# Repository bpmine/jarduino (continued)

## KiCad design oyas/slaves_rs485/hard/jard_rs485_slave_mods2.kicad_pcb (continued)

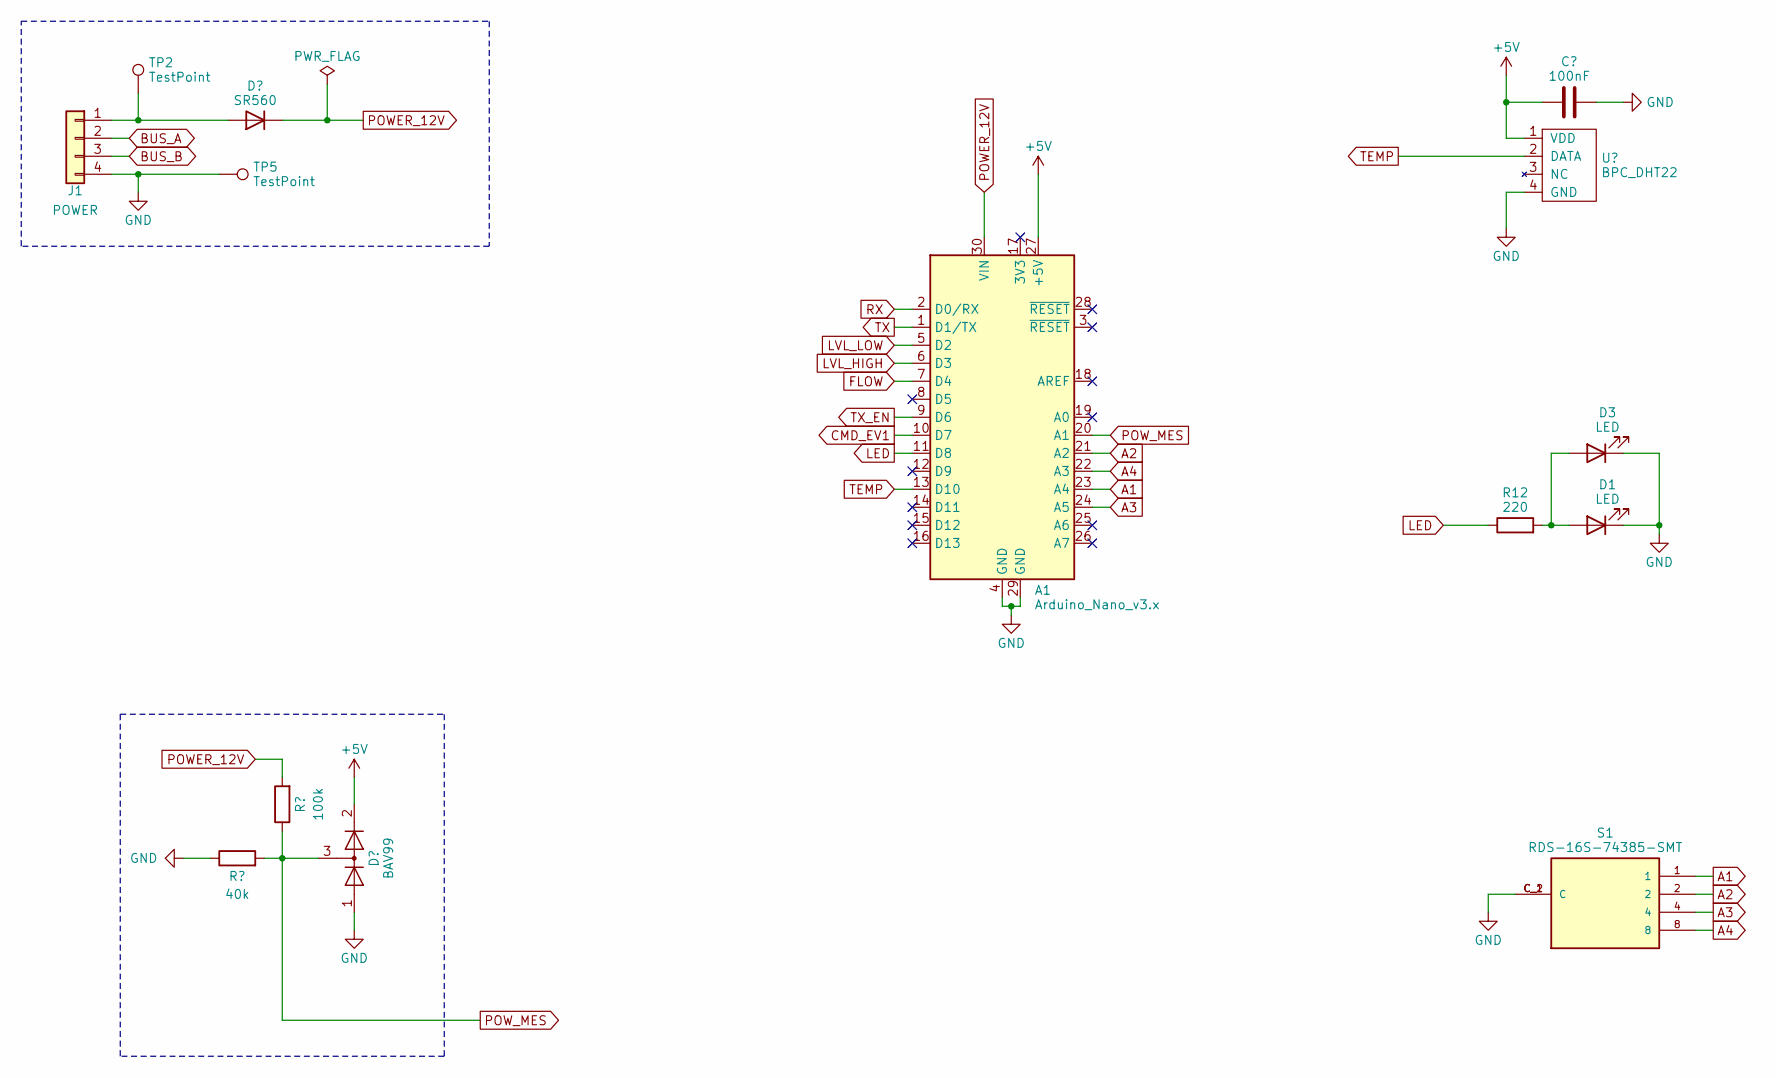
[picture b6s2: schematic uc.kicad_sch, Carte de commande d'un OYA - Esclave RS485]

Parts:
A1: Arduino_Nano_v3.x; BPC_Arduino_Nano
C7: 100nF; C_0603_1608Metric
D1: LED; LED_0805_2012Metric_Pad1.15x1.40mm_HandSolder
D2: SR560; D_DO-15_P12.70mm_Horizontal
D3: LED; LED_D3.0mm_FlatTop
D5: BAV99; SOT-23
J1: POWER; TerminalBlock_Phoenix_MKDS-1,5-4-5.08_1x04_P5.08mm_Horizont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
R1: 40k; R_0805_2012Metric_Pad1.20x1.40mm_HandSolder
R2: 100k; R_0805_2012Metric_Pad1.20x1.40mm_HandSolder
R12: 220; R_0805_2012Metric_Pad1.20x1.40mm_HandSolder
S1: RDS-16S-74385-SMT; BPC_RDS-16S-74385-SMT; PARTREV 1.0
TP2, TP5: TestPoint; TestPoint_Pad_D1.5mm
U6: BPC_DHT22

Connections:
+5V: A1.27 (+5V), C7.1, D5.2 (A), U6.1 (VDD); also elsewhere on the board
A1: A1.23 (A4), S1.1
A2: A1.21 (A2), S1.2
A3: A1.24 (A5), S1.4
A4: A1.22 (A3), S1.8
CMD_EV1: A1.10 (D7); also elsewhere on the board
FLOW: A1.7 (D4); also elsewhere on the board
GND: A1.4 (GND), A1.29 (GND), C7.2, D1.1 (K), D3.1 (K), D5.1 (K), J1.4, R1.1, S1.C_1 (C), S1.C_2 (C), TP5.1, U6.4 (GND); also elsewhere on the board
LED: A1.11 (D8), R12.1
LVL_HIGH: A1.6 (D3); also elsewhere on the board
LVL_LOW: A1.5 (D2); also elsewhere on the board
unnamed: D1.2 (A), D3.2 (A), R12.2
unnamed: D2.2 (A), J1.1, TP2.1
POWER_12V: A1.30 (VIN), D2.1 (K), R2.2; also elsewhere on the board
POW_MES: A1.20 (A1), D5.3 (K), R1.2, R2.1
TEMP: A1.13 (D10), U6.2 (DATA)
TX: A1.1 (D1/TX); also elsewhere on the board
TX_EN: A1.9 (D6); also elsewhere on the board

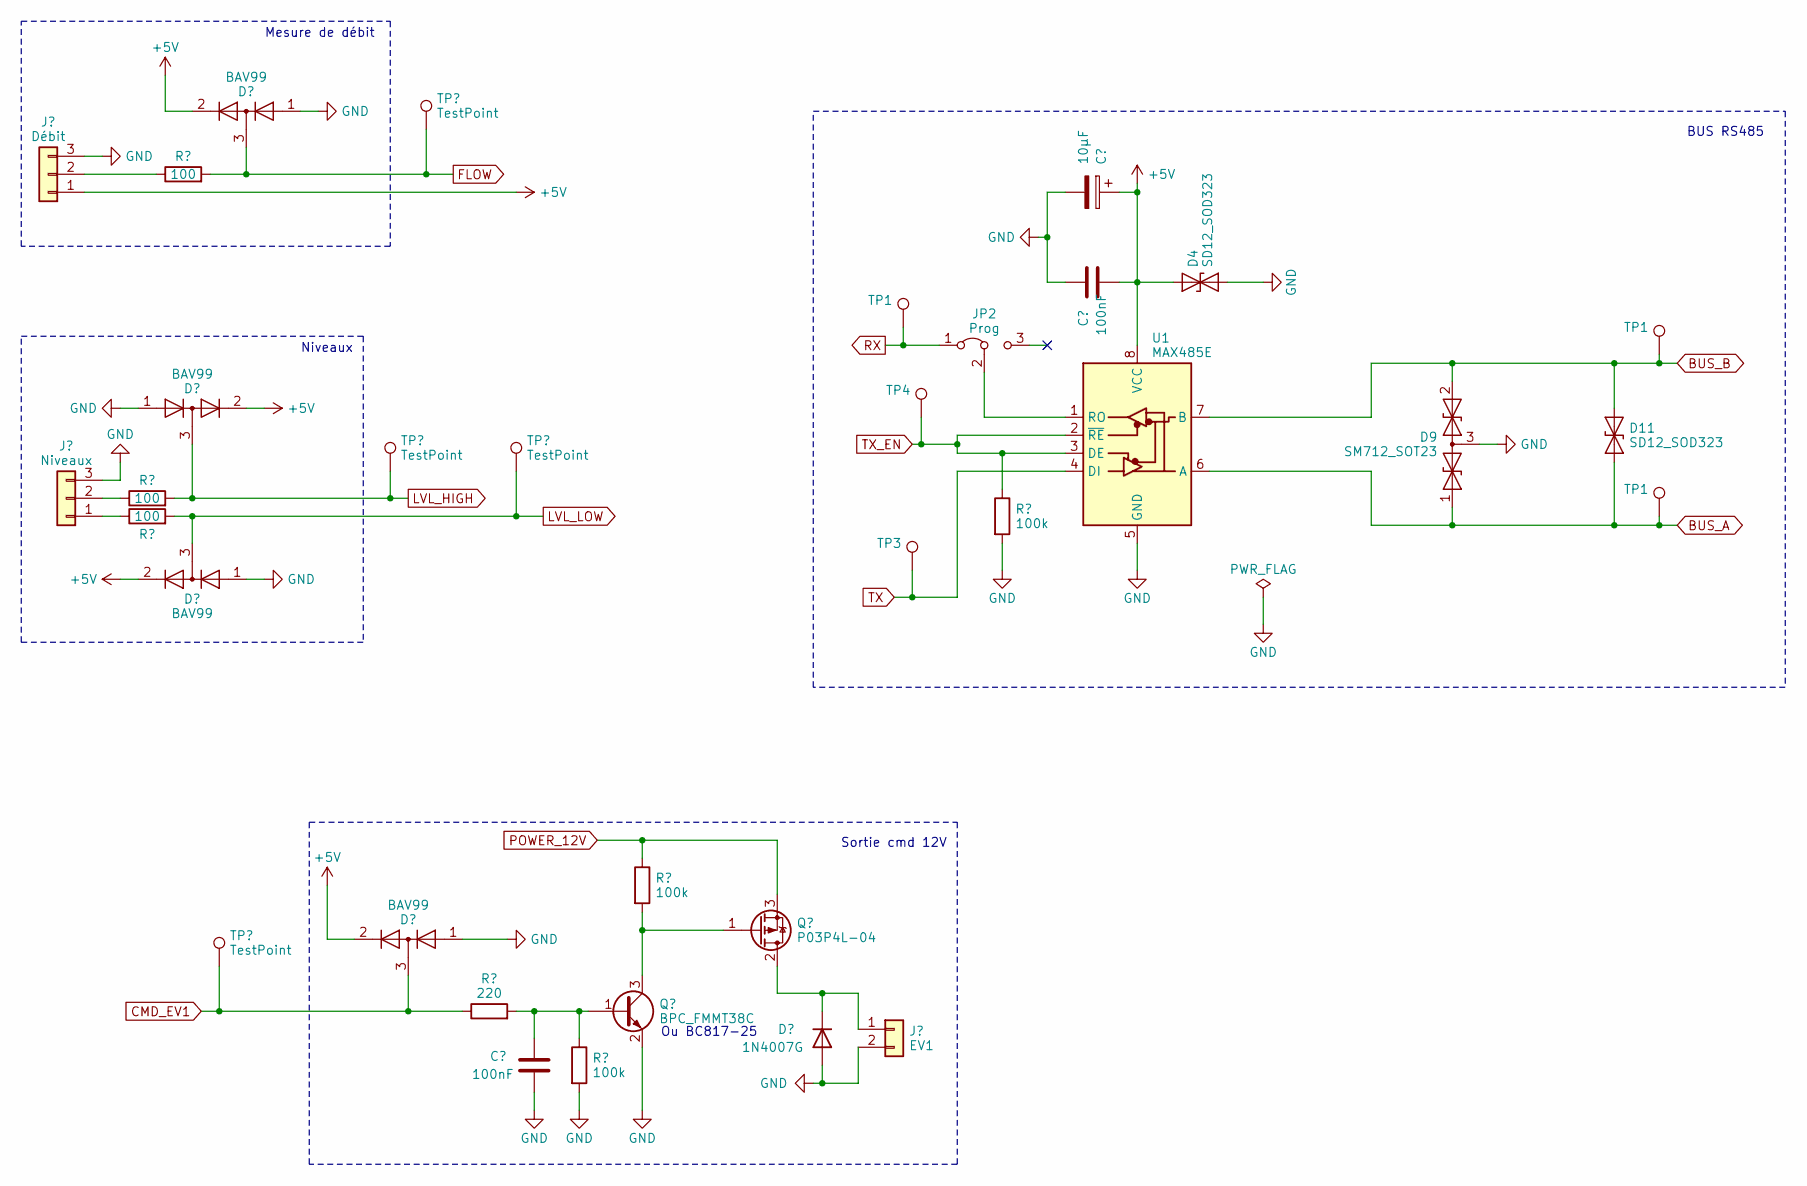
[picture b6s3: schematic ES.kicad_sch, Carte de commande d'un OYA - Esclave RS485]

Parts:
C1: 10µF; C_0805_2012Metric
C2, C6: 100nF; C_0603_1608Metric
D4, D11: SD12_SOD323; D_SOD-323
D6, D7, D8, D10: BAV99; SOT-23
D9: SM712_SOT23; SOT-23
D13: 1N4007G; D_A-405_P5.08mm_Vertical_KathodeUp
J3: Débit; TerminalBlock_Phoenix_MPT-0,5-3-2.54_1x03_P2.54mm_Horizontal
J4: Niveaux; TerminalBlock_Phoenix_MPT-0,5-3-2.54_1x03_P2.54mm_Horizontal
J6: EV1; TerminalBlock_Phoenix_MPT-0,5-2-2.54_1x02_P2.54mm_Horizontal
JP2: Prog; PinHeader_1x03_P2.54mm_Vertical
Q4: BPC_FMMT38C; BPC_SOT-23-3
Q6: P03P4L-04; TO-220-3_Vertical
R3, R15, R17: 100k; R_0805_2012Metric_Pad1.20x1.40mm_HandSolder
R7, R8, R9: 100; R_0805_2012Metric_Pad1.20x1.40mm_HandSolder
R13: 220; R_0805_2012Metric_Pad1.20x1.40mm_HandSolder
TP1, TP3, TP4, TP11, TP12, TP13, TP15: TestPoint; TestPoint_Pad_D1.5mm
U1: MAX485E; BPC_MAX485E_SOIC127P600X175-8N

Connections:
+5V: C1.1, C2.2, D4.1 (A1), D6.2 (A), D7.2 (A), D8.2 (A), D10.2 (A), J3.1, U1.8 (VCC); also elsewhere on the board
CMD_EV1: D10.3 (K), R13.1, TP15.1; also elsewhere on the board
FLOW: D8.3 (K), R7.2, TP11.1; also elsewhere on the board
GND: C1.2, C2.1, C6.2, D4.2 (A2), D6.1 (K), D7.1 (K), D8.1 (K), D9.3 (common), D10.1 (K), D13.2 (A), J3.3, J4.3, J6.2, Q4.2 (E), R3.2, R15.2, U1.5 (GND); also elsewhere on the board
LVL_HIGH: D6.3 (K), R8.2, TP12.1; also elsewhere on the board
LVL_LOW: D7.3 (K), R9.2, TP13.1; also elsewhere on the board
unnamed: D13.1 (K), J6.1, Q6.2 (D)
unnamed: J3.2, R7.1
unnamed: J4.1, R9.1
unnamed: J4.2, R8.1
unnamed: JP2.2 (C), U1.1 (RO)
unnamed: C6.1, Q4.1 (B), R13.2, R15.1
unnamed: Q4.3 (C), Q6.1 (G), R17.2
POWER_12V: Q6.3 (S), R17.1; also elsewhere on the board
TX: TP3.1, U1.4 (DI); also elsewhere on the board
TX_EN: R3.1, TP4.1, U1.2 (~RE), U1.3 (DE); also elsewhere on the board

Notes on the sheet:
Mesure de débit
Ou BC817-25
BUS RS485
Sortie cmd 12V
Niveaux

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
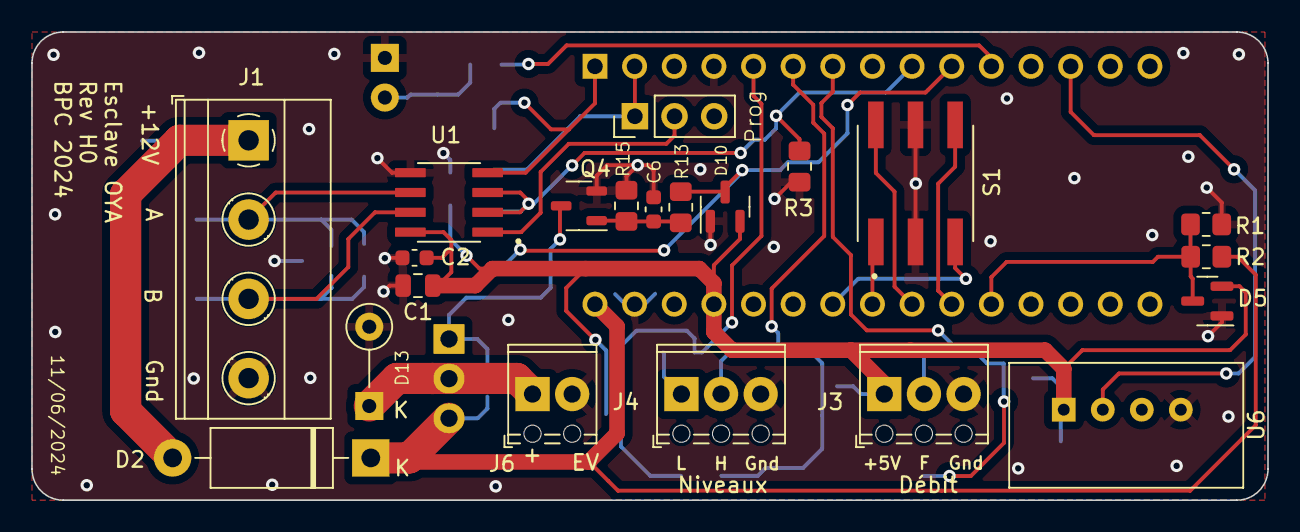
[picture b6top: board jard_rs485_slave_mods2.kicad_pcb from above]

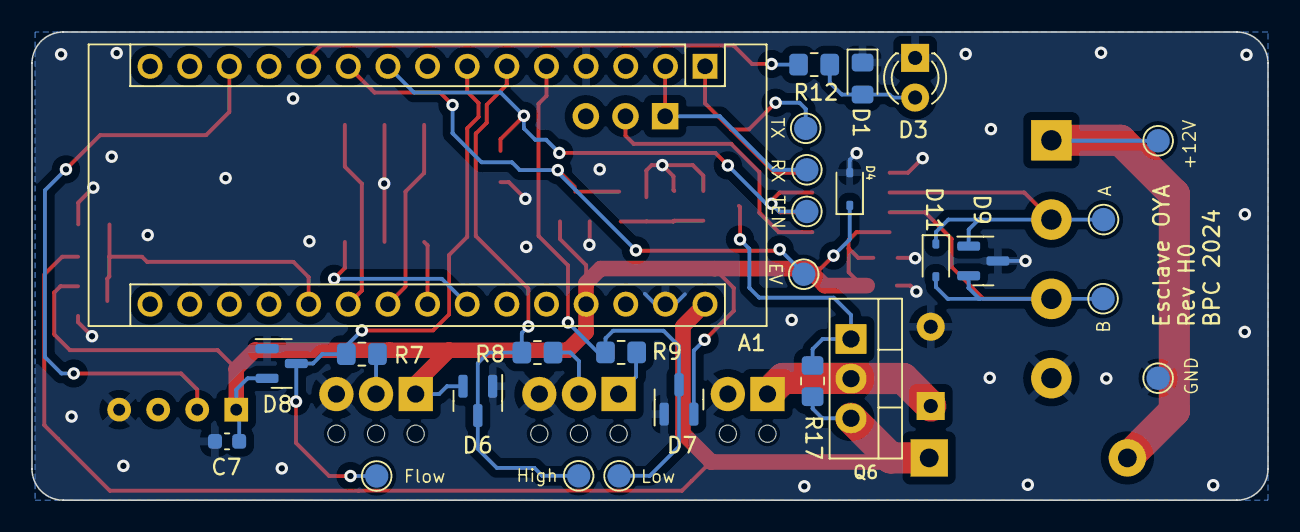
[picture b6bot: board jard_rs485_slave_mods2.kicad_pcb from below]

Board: 2 copper layers, 79.2 x 30.0 mm, 48 parts (27 on the bottom side), 28 nets.

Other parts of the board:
TP6, TP7: TestPoint; TestPoint_Pad_D1.5mm

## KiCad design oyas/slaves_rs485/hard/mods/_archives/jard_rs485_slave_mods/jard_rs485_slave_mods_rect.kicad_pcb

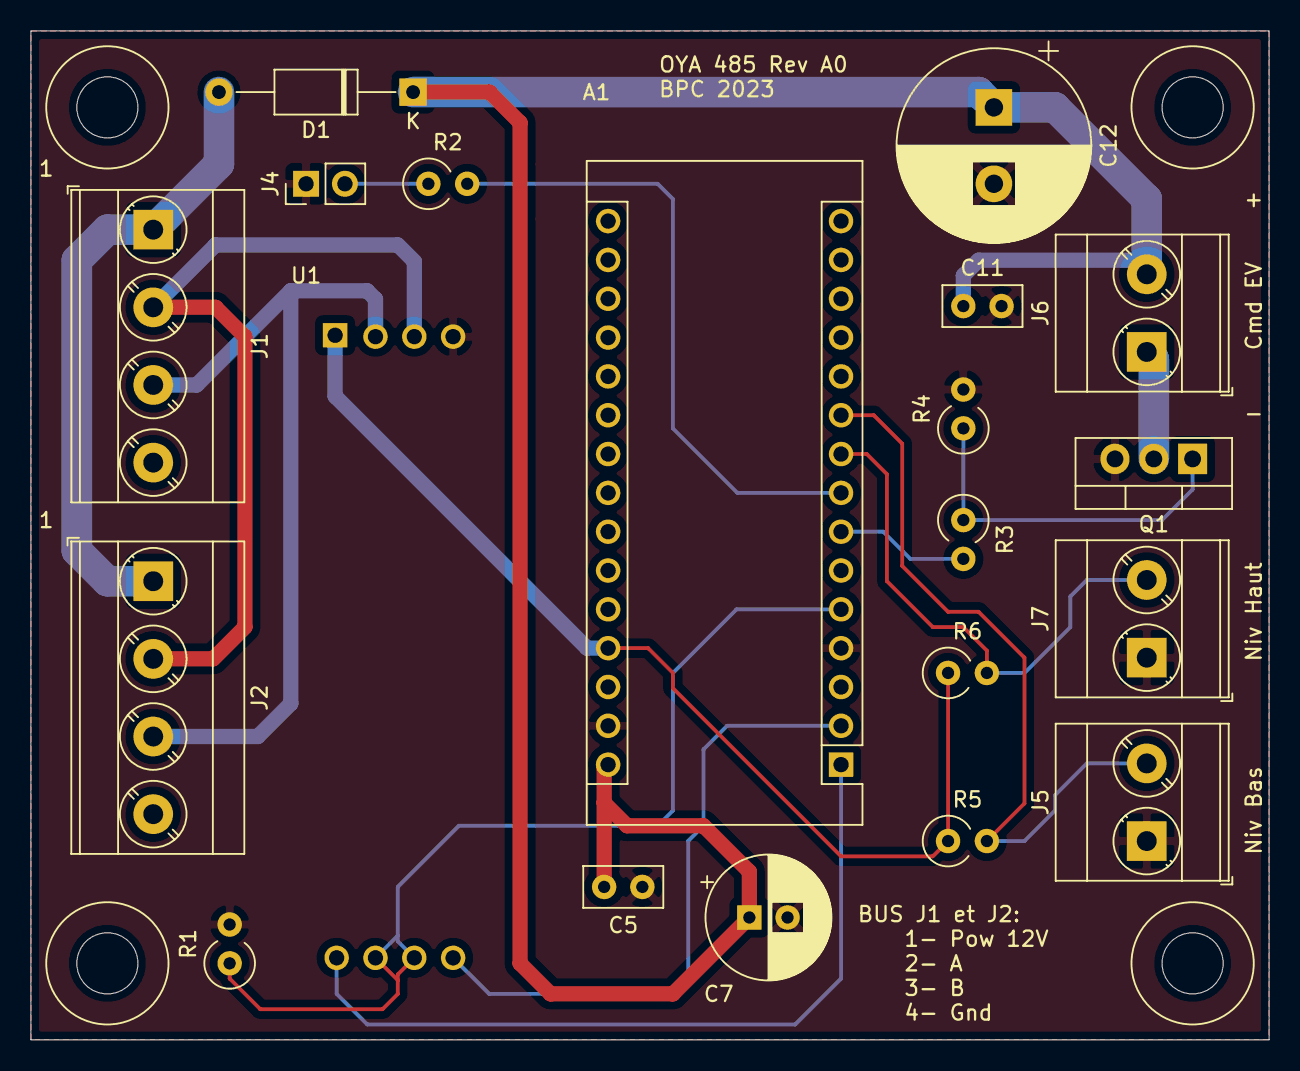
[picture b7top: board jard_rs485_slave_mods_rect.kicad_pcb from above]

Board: 2 copper layers, 81.0 x 66.0 mm, 20 parts (0 on the bottom side), 17 nets.

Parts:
A1: Arduino_Nano_v2.x; BPC_Arduino_Nano
C5: 10n; C_Disc_D5.0mm_W2.5mm_P2.50mm
C7: 10µF; CP_Radial_D8.0mm_P2.50mm
C11: 10nF; C_Disc_D5.0mm_W2.5mm_P2.50mm
C12: 20µF; CP_Radial_D12.5mm_P5.00mm
D1: D; D_A-405_P12.70mm_Horizontal
J1: NETWORK IN; TerminalBlock_Phoenix_MKDS-3-4-5.08_1x04_P5.08mm_Horizontal
J2: NETWORK OUT; TerminalBlock_Phoenix_MKDS-3-4-5.08_1x04_P5.08mm_Horizontal
J4: LED; PinHeader_1x02_P2.54mm_Vertical
J5: Niveau bas; TerminalBlock_Phoenix_MKDS-3-2-5.08_1x02_P5.08mm_Horizontal
J6: Electrovanne 12V; TerminalBlock_Phoenix_MKDS-3-2-5.08_1x02_P5.08mm_Horizontal
J7: Niveau Haut; TerminalBlock_Phoenix_MKDS-3-2-5.08_1x02_P5.08mm_Horizontal
Q1: TIP41C; TO-220-3_Vertical
R1, R4, R5, R6: 100k; R_Axial_DIN0309_L9.0mm_D3.2mm_P2.54mm_Vertical
R2: 150; R_Axial_DIN0309_L9.0mm_D3.2mm_P2.54mm_Vertical
R3: 50; R_Axial_DIN0309_L9.0mm_D3.2mm_P2.54mm_Vertical
U1: BPC_Mod485

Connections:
CMD_EV: A1.7, R3.2
GND: A1.4, A1.29, C5.1, C7.2, C11.2, C12.2, J4.1, J5.1, J7.1, Q1.3, R1.2, R4.2, U1.4
IN_LVL_HIGH: A1.9, J7.2, R6.2
IN_LVL_LOW: A1.10, J5.2, R5.2
unnamed: A1.8, R2.2
unnamed: A1.30, C5.2, C7.1, C11.1, C12.1, D1.1, J6.2
unnamed: D1.2, J1.1, J2.1
unnamed: J1.2, J2.2, U1.3
unnamed: J1.3, J2.3, U1.2
unnamed: J1.4, J2.4
unnamed: J4.2, R2.1
unnamed: J6.1, Q1.2
unnamed: Q1.1, R3.1, R4.1
RX: A1.2, U1.5
TX: A1.1, U1.8
TXEN: A1.5, R1.1, U1.6, U1.7
Vcc: A1.27, R5.1, R6.1, U1.1
